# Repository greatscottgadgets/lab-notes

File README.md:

# lab-notes
notes, test reports, and other documentation for projects in progress

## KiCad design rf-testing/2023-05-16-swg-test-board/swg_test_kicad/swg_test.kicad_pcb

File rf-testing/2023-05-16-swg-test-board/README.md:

# 2023-05-16 SWG Test Board

## Description

The purpose of this board is to evaluate performance of Murata SWG-series switchable RF test connectors. These connectors can be placed in series with a transmission line and usually act as a through connection. When a probe is attached, the through connection is broken and one side of the tranmission line is connected to the probe.

This makes it easy to reliably test separate blocks of a design, without having to build them as separate modules needing to be cabled together.

The test board includes 2xThru structures designed to be used with the [IEEEP370 de-embedding algorithms](https://scikit-rf.readthedocs.io/en/latest/examples/networktheory/IEEEP370%20Deembedding.html).

## Results

### Importance of 2xThru length

Unfortunately, there is limited advice available on how to design a good 2xThru structure. One piece of advice is to make the structure at least a certain length, depending on the total bandwidth of the S-parameter measurements ([this article from Copper Mountain](https://coppermountaintech.com/eliminating-fixture-effects-from-embedded-measurements/) recommends 2.4" for 9 GHz bandwidth). This is because the de-embedding algorithm uses the time-domain transform to gate each half of the fixture, and the time (and length) resolution is limited by bandwidth.

I thought that this wouldn't be a problem on this test board, because the SWG probes themselves have a long pig-tail and this makes the overall thru length long enough. However, running the algorithm generates fixture S-parameters with an unexpected spike at the end of the frequency range:

A check recommended by the specification is to use the generated fixture S-parameters to de-embed the orignal Thru, and the residual S21 magnitude and phase should be very close to 0, but this check also shows a large spike at the end:

An [issue raised on the scikit-rf repository](https://github.com/scikit-rf/scikit-rf/issues/825) suggests that this can be caused by using a 2xThru where the middle impedance section is too short.

After looking further into the algorithm, I think I understand why this is. For finding S11 of the first fixture, for example, it takes S11 of the Thru and converts it to time domain, giving a plot of impulses against time. It then finds the mid-point, zeroes out the second half of the data, and converts back to frequency domain. If the length of uniform impedance in the middle is too short, then the edges of any impulses can overlap the mid-point and so setting the second half to zero causes a sudden step which shows up as high-frequency content when converted back to the frequency domain.

So, for future fixtures, I think the appropriate advice is to make sure that the 2xThru structure contains a section of uniform impedance in the middle that is at least 2.4" (for 9 GHz, as suggested above), rather than looking at the length of the whole structure.

While the SWG Thru trace is too short to be reliable, the U.FL trace is much closer to the minimum so that has been used below (though it still shows some artifacts at the top end of the frequency range).

### SWG Insertion Loss

By using the `U.FL Thru` trace as a 2xThru structure to de-embed measurement of the `SWG Thru Test` trace, we can measure the effect of placing an SWG connector on the transmission line:

Performance looks very good with insertion loss below 0.2dB out to beyond 6 GHz, so I'm confident that these connectors can be used in future test boards without having any significant impact on the rest of the circuit.

### U.FL footprint

For this board, I used that standard KiCad library footprint for the U.FL connector. However, it has a fairly significant mismatch:

I think this is due to the large signal pad, the wide trace on the bottom of the connector itself, and the proxmity to the ground plane on layer 2. I think it could benefit from a ground cutout similar to previous SMA connector test boards.

#### Update (2023-05-23):

I realised I could try the ground cutout fairly easily by milling slots in the back of the PCB:

This improved things a lot, reducing the mismatch to ~6 ohms, but could still be improved further:

(The yellow trace is the unmodified board, green is the modified board)

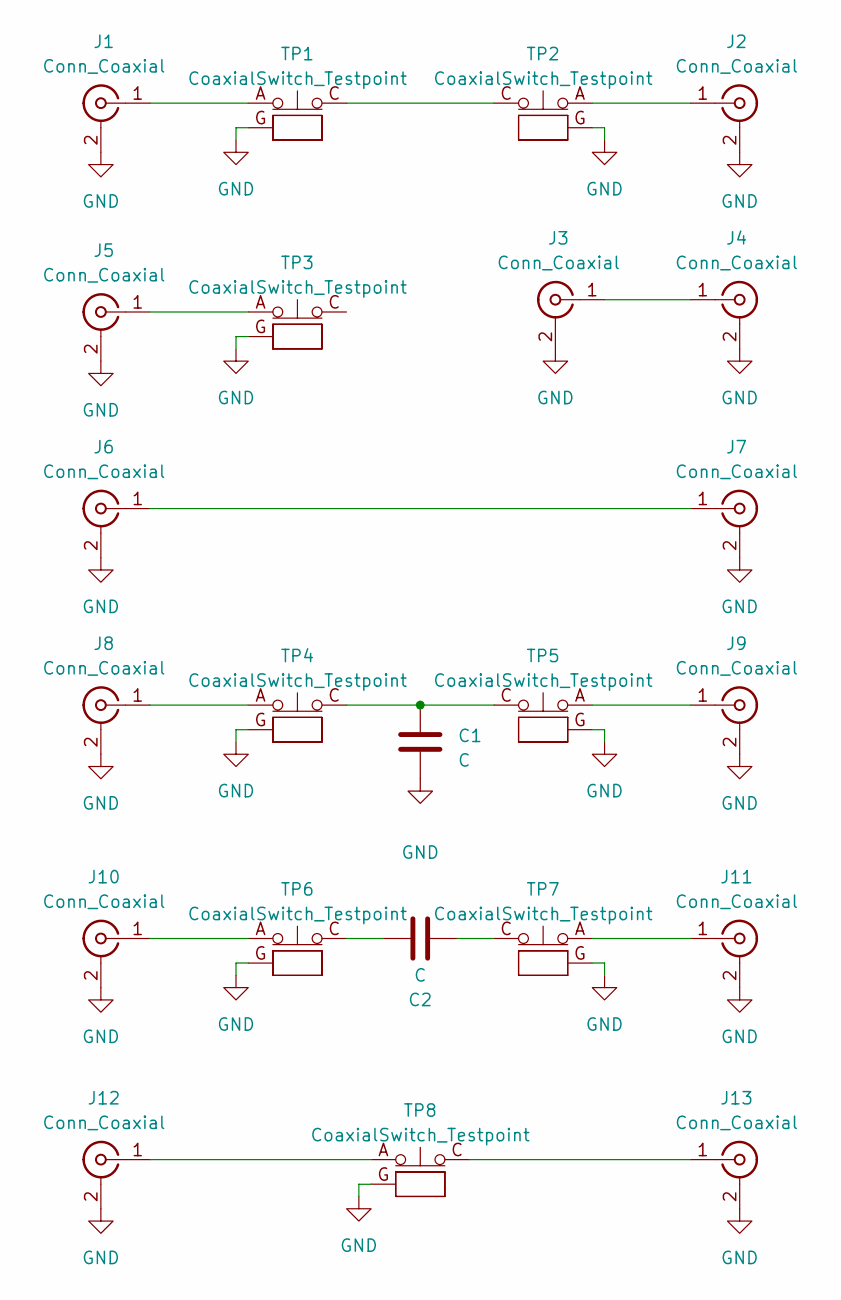
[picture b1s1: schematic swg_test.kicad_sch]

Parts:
C1, C2: C; C_0402_1005Metric
J1, J2, J3, J4, J5, J6, J7, J8, J9, J10, J11, J12, J13: Conn_Coaxial; U.FL_Hirose_U.FL-R-SMT-1_Vertical
TP1, TP2, TP3, TP4, TP5, TP6, TP7, TP8: CoaxialSwitch_Testpoint; CoaxialSwitch_Murata_MM8030-2610

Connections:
GND: C1.2, J1.2 (Ext), J2.2 (Ext), J3.2 (Ext), J4.2 (Ext), J5.2 (Ext), J6.2 (Ext), J7.2 (Ext), J8.2 (Ext), J9.2 (Ext), J10.2 (Ext), J11.2 (Ext), J12.2 (Ext), J13.2 (Ext), TP1.G, TP2.G, TP3.G, TP4.G, TP5.G, TP6.G, TP7.G, TP8.G
unnamed: C1.1, TP4.C, TP5.C
unnamed: C2.1, TP6.C
unnamed: C2.2, TP7.C
unnamed: J1.1 (In), TP1.A
unnamed: J2.1 (In), TP2.A
unnamed: J3.1 (In), J4.1 (In)
unnamed: J5.1 (In), TP3.A
unnamed: J6.1 (In), J7.1 (In)
unnamed: J8.1 (In), TP4.A
unnamed: J9.1 (In), TP5.A
unnamed: J10.1 (In), TP6.A
unnamed: J11.1 (In), TP7.A
unnamed: J12.1 (In), TP8.A
unnamed: J13.1 (In), TP8.C
unnamed: TP1.C, TP2.C

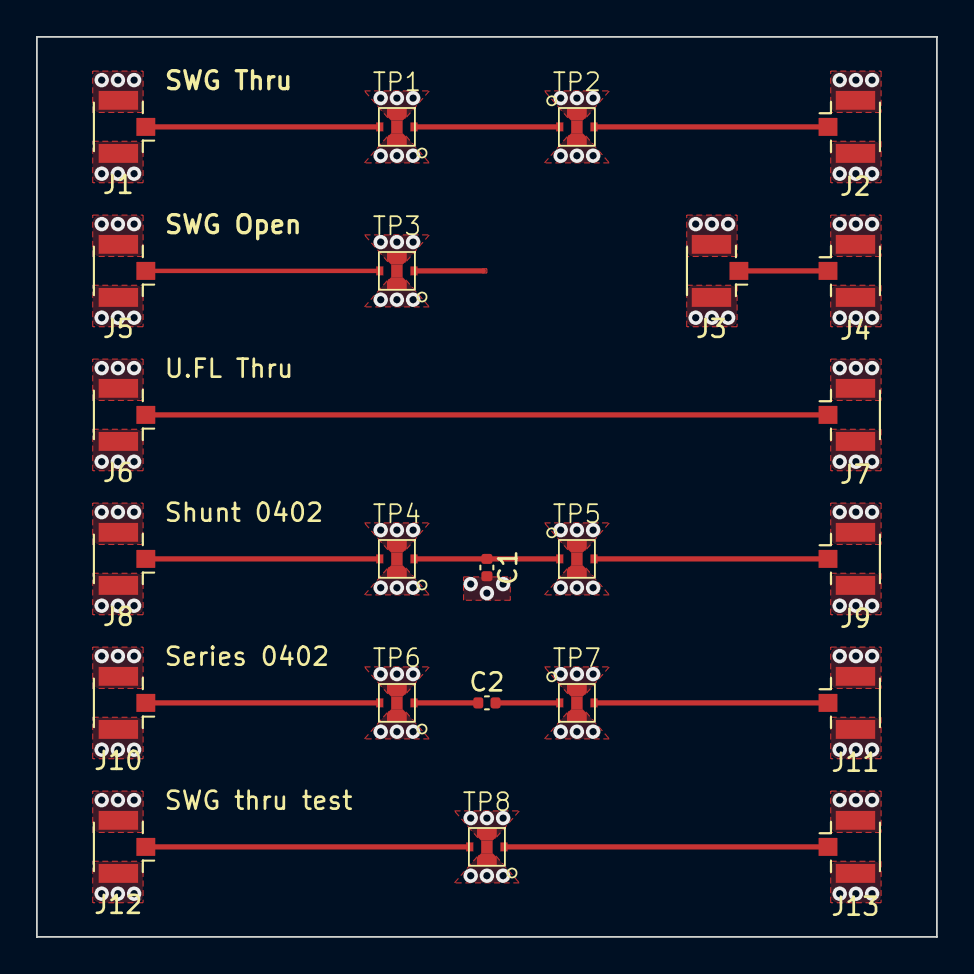
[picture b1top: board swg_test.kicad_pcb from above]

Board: 4 copper layers, 50.0 x 50.0 mm, 23 parts (0 on the bottom side), 16 nets.

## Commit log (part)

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2023-04-12 add rf-switches-2023-04-09.md
    component search notes
2023-04-12 fix markdown
2023-04-20 corrections
2023-04-20 Add report for JLCPCB SMA footprint testing
2023-04-23 RF switch updates
2023-04-26 add 2022-04-06-sma-and-trace-width-test
2023-04-26 add 2022-04-24-sma-and-trace-width-test
2023-04-26 add 2022-04-24-unun-test
2023-04-26 add 2022-04-24-limiter-test
2023-04-26 add 2022-05-04-unun-modelling
2023-04-26 add 2022-05-30-unun-test
2023-05-17 Add SWG test board
2023-05-23 SWG test: add results of modifying the boards to add a GND cutout
2023-05-26 add 2023-05-25 URTI progress report
    (phase one completion)
2023-06-02 add 2023-05-31-dpdt-switch-test
2023-06-02 edit for readability and clarity
2023-06-02 add DPDT switch test to URTI progress report
2023-06-02 update URTI progress report date
2024-01-05 Add 2024-01-05 JLC7628 trace width test board results
2024-01-05 fix TDR image path
2024-01-10 Update 2023-04-19 SMA footprint test with note about out-of-date trace width
2024-02-27 Add 2024-02-27 URTI progress report
2024-06-21 Add 2024-06-21 URTI progress report
2024-08-02 Clarify report text and add a link
2024-08-05 Update date of URTI progress report
2024-11-22 add 2024-11-20-choke-test
2024-11-22 Add 2024-11-22-sma-test
2024-11-28 Add 2024-11-27-amp-test
2024-12-06 Add 2024-12-05-limiter-test
2024-12-17 Add 2024-12-16-spdt-switch-test
2024-12-17 Add 2024-12-16-filter-test
2025-03-23 Add 2025-03-23-filter-test
2026-05-13 add 2026-05-09-luna-superspeed-improvements
